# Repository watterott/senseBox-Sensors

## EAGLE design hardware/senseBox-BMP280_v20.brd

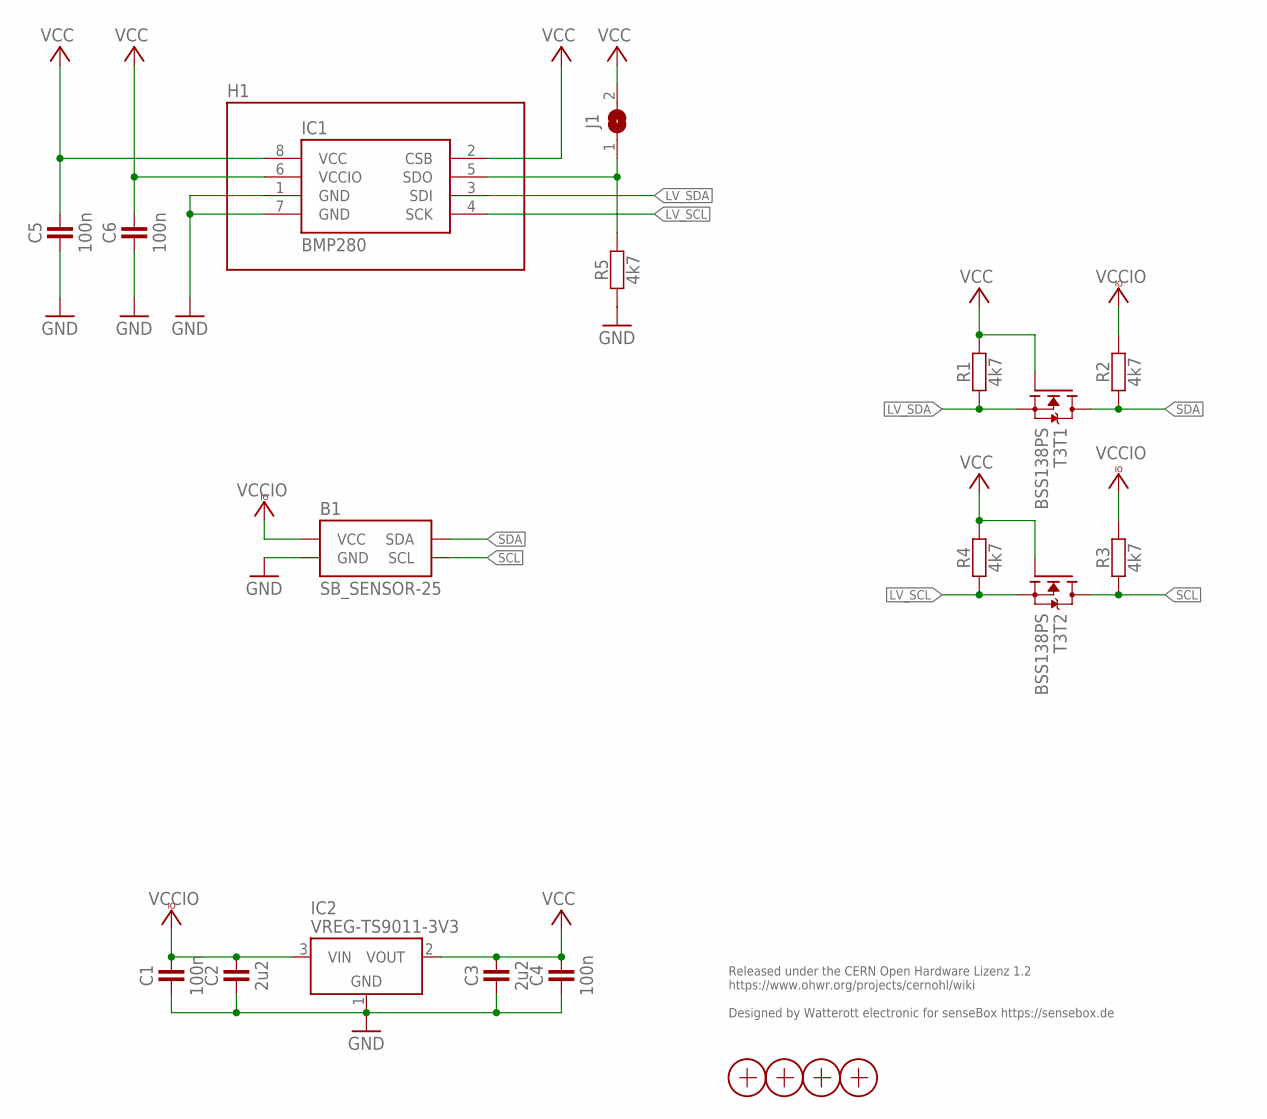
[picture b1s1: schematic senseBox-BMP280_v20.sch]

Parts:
B1: SB_SENSOR-25; SB-25X25
C1, C4, C5, C6: 100n; C0402
C2, C3: 2u2; C0402
H1: SF2
IC1: BMP280; LGA8
IC2: VREG-TS9011-3V3; SOT23
J1: JUMPER2-0402-NC; JUMPER2-0402_NC
R1, R2, R3, R4, R5: 4k7; C0402
T3: BSS138PS; SOT363
X1, X2, X3, X4: PASSER-07; PASSER_07MM

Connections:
GND: B1.GND, C1.1, C2.1, C3.1, C4.1, C5.1, C6.1, IC1.1 (GND), IC1.7 (GND), IC2.1 (GND), R5.1
LV_SCL: IC1.4 (SCK), R4.1, T3.4 (S)
LV_SDA: IC1.3 (SDI), R1.1, T3.1 (S)
LV_SDO: IC1.5 (SDO), J1.1, R5.2
SCL: B1.SCL, R3.1, T3.3 (D)
SDA: B1.SDA, R2.1, T3.6 (D)
VCC: C3.2, C4.2, C5.2, C6.2, IC1.2 (CSB), IC1.6 (VCCIO), IC1.8 (VCC), IC2.2 (VOUT), J1.2, R1.2, R4.2, T3.2 (G), T3.5 (G)
VCCIO: B1.VCC, C1.2, C2.2, IC2.3 (VIN), R2.2, R3.2

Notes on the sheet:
Released under the CERN Open Hardware Lizenz 1.2 https://www.ohwr.org/projects/cernohl/wiki Designed by Watterott electronic for senseBox https://sensebox.de

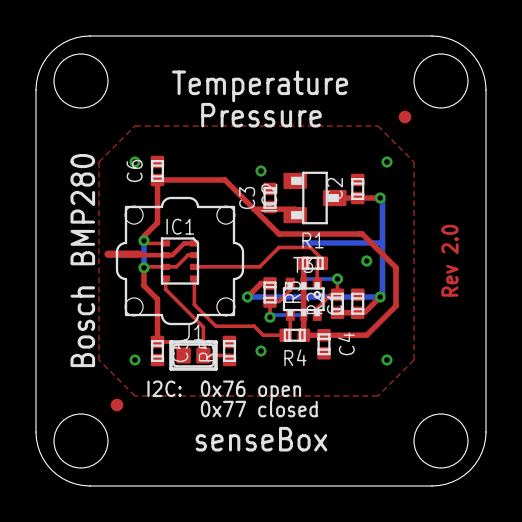
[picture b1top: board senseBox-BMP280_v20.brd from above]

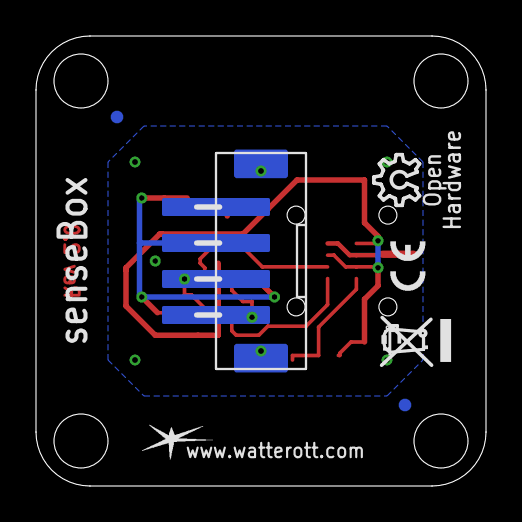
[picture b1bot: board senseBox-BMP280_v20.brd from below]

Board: 2 copper layers, 25.0 x 25.0 mm, 21 parts (2 on the bottom side), 8 nets.

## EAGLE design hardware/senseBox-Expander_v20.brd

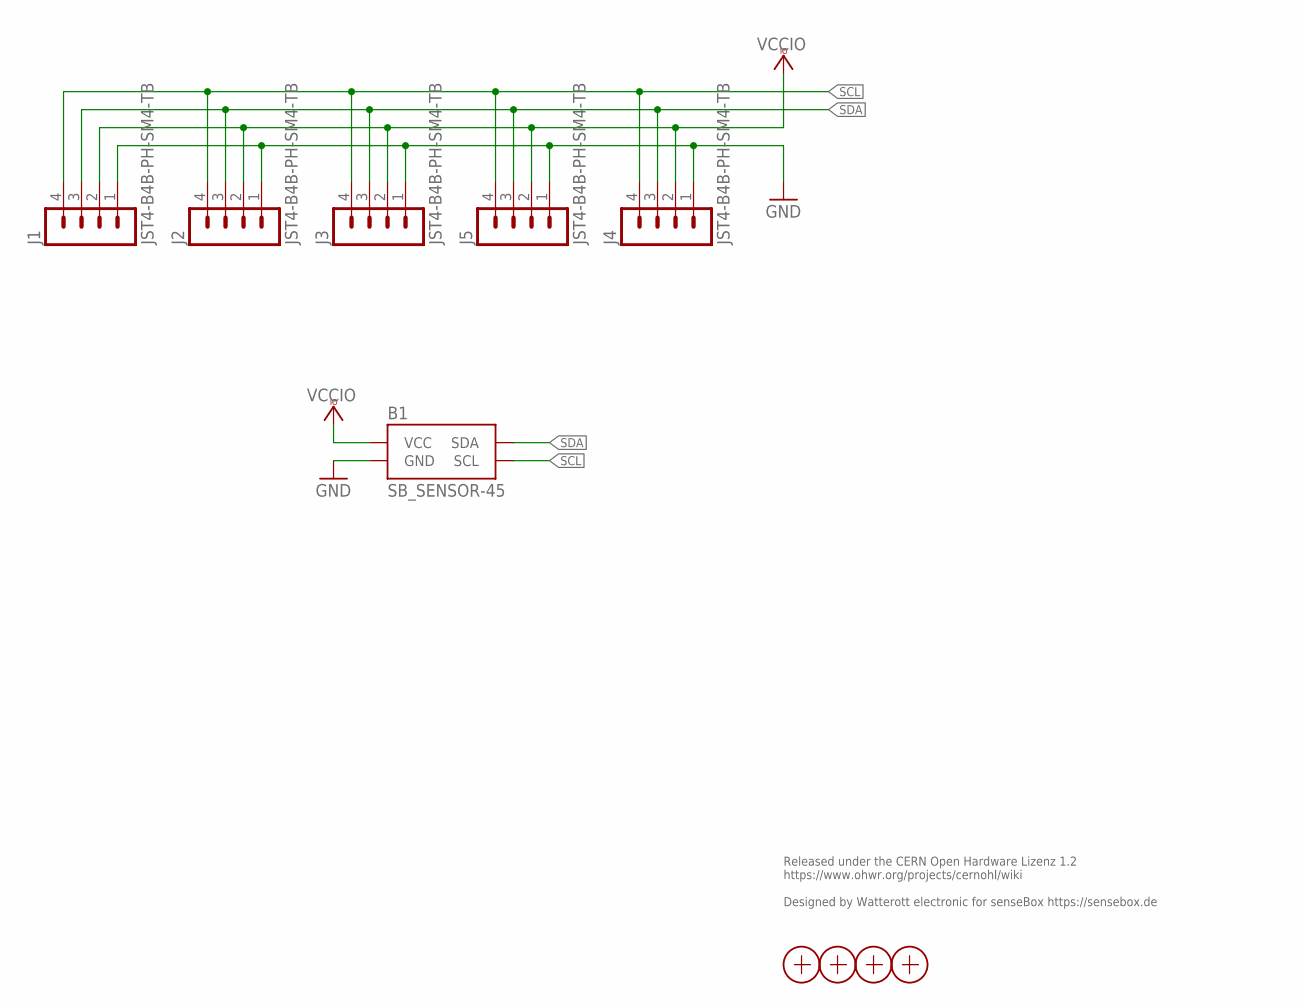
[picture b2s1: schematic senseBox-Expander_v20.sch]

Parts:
B1: SB_SENSOR-45; SB-45X25
J1, J2, J3, J4, J5: JST4-B4B-PH-SM4-TB; JST_B4B-PH-SM4-TB
X1, X2, X3, X4: PASSER-07; PASSER_07MM

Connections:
GND: B1.GND, J1.1, J2.1, J3.1, J4.1, J5.1
SCL: B1.SCL, J1.4, J2.4, J3.4, J4.4, J5.4
SDA: B1.SDA, J1.3, J2.3, J3.3, J4.3, J5.3
VCCIO: B1.VCC, J1.2, J2.2, J3.2, J4.2, J5.2

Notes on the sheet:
Released under the CERN Open Hardware Lizenz 1.2 https://www.ohwr.org/projects/cernohl/wiki Designed by Watterott electronic for senseBox https://sensebox.de

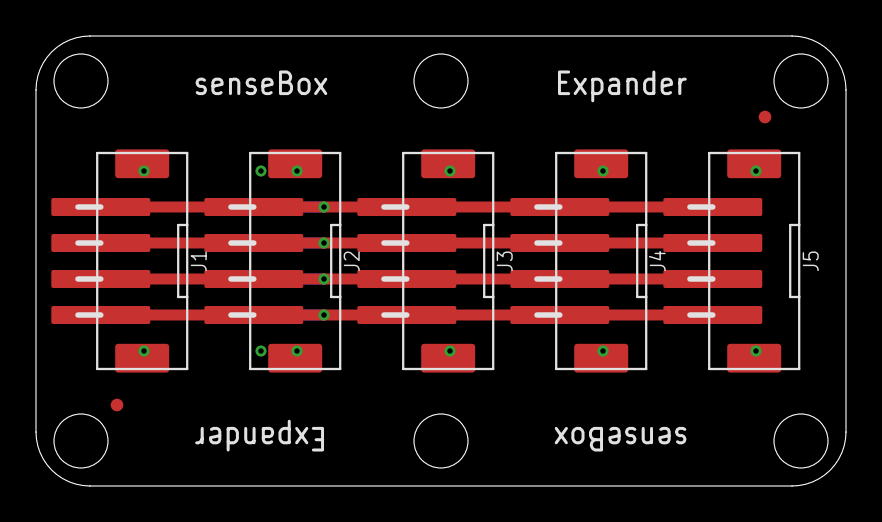
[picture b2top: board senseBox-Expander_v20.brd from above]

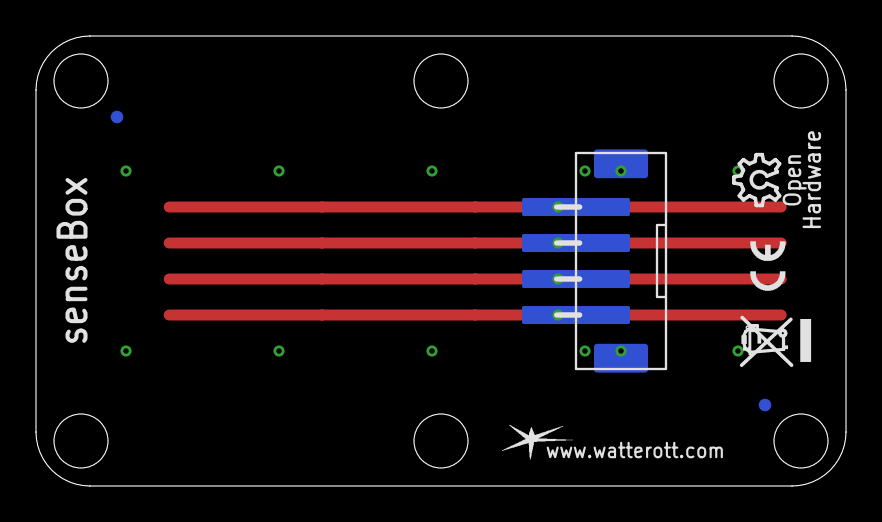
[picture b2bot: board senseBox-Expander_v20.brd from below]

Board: 2 copper layers, 45.0 x 25.0 mm, 10 parts (2 on the bottom side), 4 nets.

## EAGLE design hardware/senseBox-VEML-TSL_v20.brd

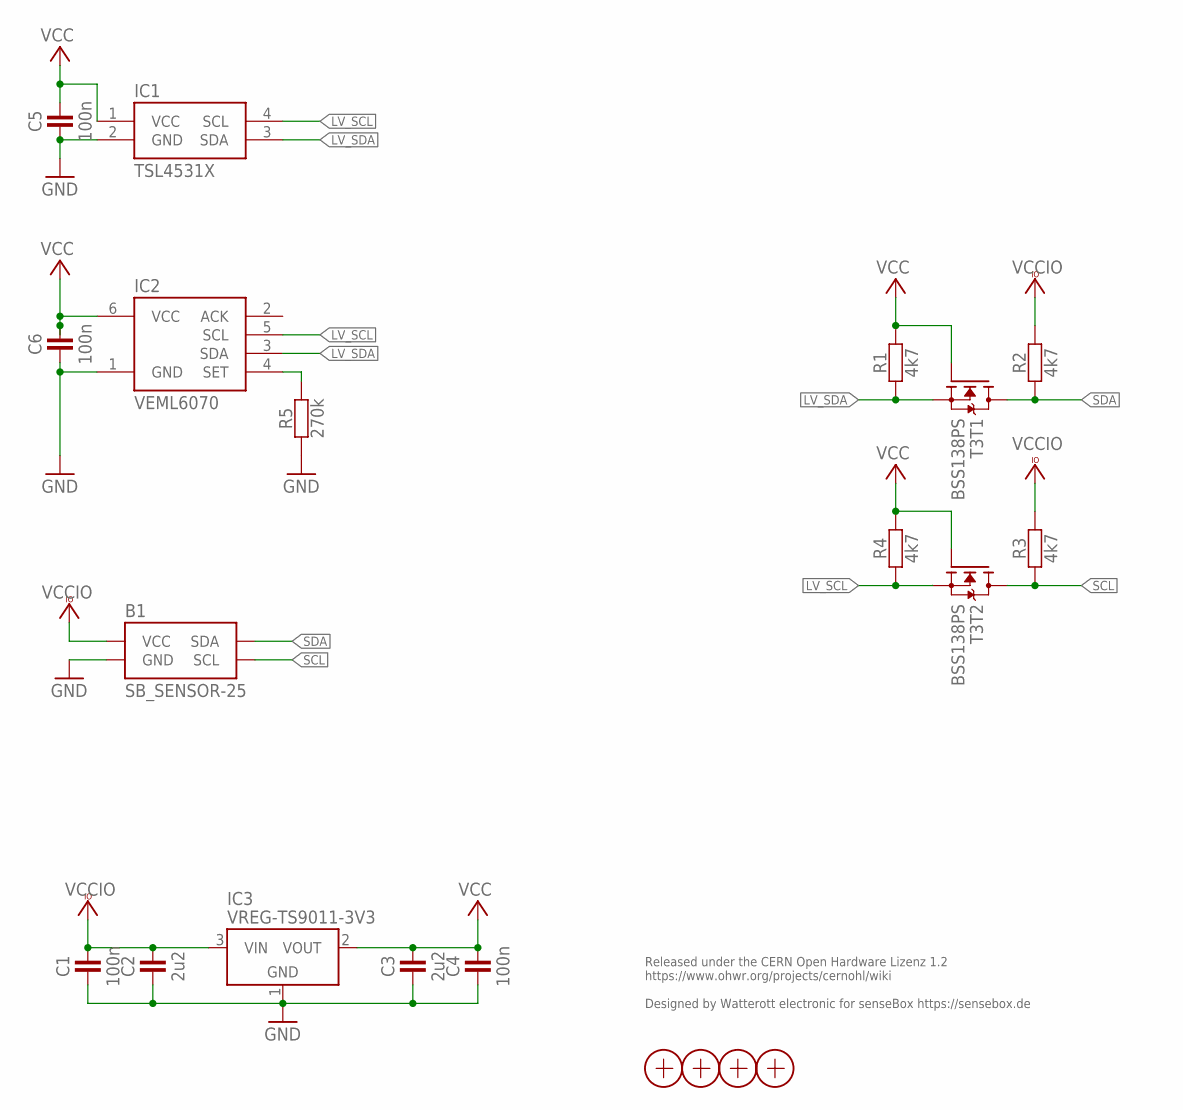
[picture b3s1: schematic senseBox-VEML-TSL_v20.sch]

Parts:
B1: SB_SENSOR-25; SB-25X25
C1, C4, C5, C6: 100n; C0402
C2, C3: 2u2; C0402
IC1: TSL4531X; AMS_CL
IC2: VEML6070; OPLGA
IC3: VREG-TS9011-3V3; SOT23
R1, R2, R3, R4: 4k7; C0402
R5: 270k; C0402
T3: BSS138PS; SOT363
X1, X2, X3, X4: PASSER-07; PASSER_07MM

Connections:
GND: B1.GND, C1.1, C2.1, C3.1, C4.1, C5.1, C6.1, IC1.2 (GND), IC2.1 (GND), IC3.1 (GND), R5.1
LV_SCL: IC1.4 (SCL), IC2.5 (SCL), R4.1, T3.4 (S)
LV_SDA: IC1.3 (SDA), IC2.3 (SDA), R1.1, T3.1 (S)
SCL: B1.SCL, R3.1, T3.3 (D)
SDA: B1.SDA, R2.1, T3.6 (D)
SET: IC2.4 (SET), R5.2
VCC: C3.2, C4.2, C5.2, C6.2, IC1.1 (VCC), IC2.6 (VCC), IC3.2 (VOUT), R1.2, R4.2, T3.2 (G), T3.5 (G)
VCCIO: B1.VCC, C1.2, C2.2, IC3.3 (VIN), R2.2, R3.2

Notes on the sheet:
Released under the CERN Open Hardware Lizenz 1.2 https://www.ohwr.org/projects/cernohl/wiki Designed by Watterott electronic for senseBox https://sensebox.de

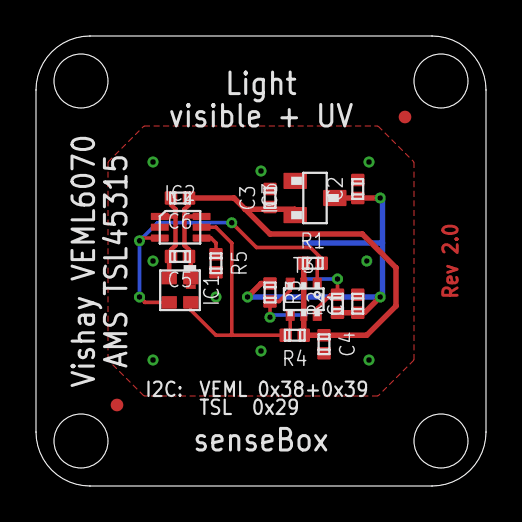
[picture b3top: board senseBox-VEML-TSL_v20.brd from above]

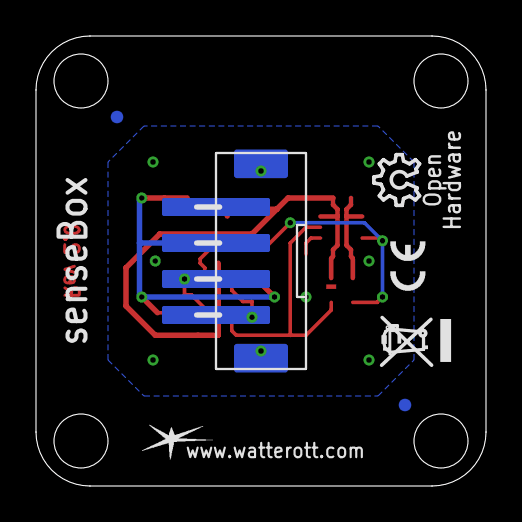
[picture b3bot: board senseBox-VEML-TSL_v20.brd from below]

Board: 2 copper layers, 25.0 x 25.0 mm, 20 parts (2 on the bottom side), 8 nets.
